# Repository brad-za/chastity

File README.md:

# Chastity Keyboard - Choc v1

A wireless split ergonomic keyboard featuring Kailh Choc v1 low-profile switches, rotary encoders, and ZMK firmware.

## Features

- **Split Design**: Ergonomic 30-key split layout per half (60 keys total)
- **Wireless**: Powered by nice!nano v2 controllers with ZMK firmware
- **Low Profile**: Kailh Choc v1 switches for a sleek, portable design
- **Rotary Encoders**: One encoder per half for volume/scroll control
- **Hot-swap**: Choc v1 hot-swap sockets for easy switch replacement
- **Battery Powered**: Individual LiPo batteries for each half
- **Power Management**: Individual power switches per half

## Bill of Materials (BOM)

### Electronics & Controllers
| Component | Quantity | Description | Notes |
|-----------|----------|-------------|-------|
| nice!nano v2 | 2 | Wireless microcontroller | One per half |
| LiPo Battery | 2 | 3.7V 110-301230 or similar | ~110mAh recommended |
| JST PH 2-pin Connector | 2 | Battery connector | For nice!nano battery connection |

### Switches & Keycaps
| Component | Quantity | Description | Notes |
|-----------|----------|-------------|-------|
| Kailh Choc v1 Switches | 60 | Low-profile mechanical switches | Any Choc v1 variant |
| Choc v1 Keycaps (1u) | 54 | Standard 1u keycaps | |
| Choc v1 Keycaps (1u) | 2 | Indexed 1u keycaps | F & J keys |
| Choc v1 Keycaps (1.25u) | 2 | Pinky key keycaps | For control buttons cluster |
| Choc v1 Keycaps (1.5u) | 2 | Thumb key keycaps | For thumb cluster |

### Electronic Components
| Component | Quantity | Description | Package | Notes |
|-----------|----------|-------------|---------|-------|
| Diodes | 60 | 1N4148W or similar | SOD-123 | One per switch |
| Rotary Encoder | 2 | Alps EC11E series | Through-hole | With push switch |
| Power Switch | 2 | SPDT slide switch | PCM12 package | Individual power control |
| Choc v1 Hot-swap Sockets | 60 | Kailh hot-swap sockets | | One per switch position |

### PCBs & Hardware
| Component | Quantity | Description | Notes |
|-----------|----------|-------------|-------|
| Chastity PCB Left | 1 | Main PCB for left half | Fabricate from KiCad files |
| Chastity PCB Right | 1 | Main PCB for right half | Fabricate from KiCad files |
| Case Components | 1 set | Laser-cut case files | Optional - see cases/choc/v1/ |

### Optional Components
| Component | Quantity | Description | Notes |
|-----------|----------|-------------|-------|
| USB-C Cable | 2 | Charging/programming | Standard USB-C cables |

## Assembly Instructions

### 1. PCB Preparation
1. Inspect PCBs for any manufacturing defects
2. Clean flux residue if necessary

### 2. SMD Component Soldering
1. **Diodes**: Solder all 60 diodes (30 per PCB) in SOD-123 packages
   - Pay attention to polarity markings on the PCB
   - Cathode (marked end) should align with the line on the PCB silkscreen

### 3. Through-hole Components
1. **Hot-swap sockets**: Install all 60 Choc v1 hot-swap sockets
   - Ensure proper alignment before soldering
   - Apply flux for clean joints
2. **Rotary encoders**: Install one Alps EC11E encoder per PCB
   - Ensure proper seating before soldering
3. **Power switches**: Install PCM12 slide switches
4. **Battery connectors**: Install JST PH 2-pin connectors

### 4. Controller Installation
1. **Socket installation** (recommended):
   - Install mill-max sockets for nice!nano controllers
   - This allows for easy removal/replacement
2. **nice!nano mounting**:
   - Install nice!nano v2 controllers with components facing down
   - Ensure proper pin alignment

### 5. Switch Installation
1. Install Kailh Choc v1 switches into hot-swap sockets
2. Ensure switches are fully seated and secure
3. Test each switch for proper actuation

### 6. Keycap Installation
1. Install keycaps on all switches
2. Use 1.25u keycaps for thumb cluster keys

## Firmware

This keyboard uses ZMK firmware with configurations located in `code/zmk/`.

### Flashing Firmware

#### Initial Setup
1. Connect nice!nano via USB-C
2. Put controller in bootloader mode (double-tap reset)
3. Flash the appropriate firmware:
   - `chastity_left-nice_nano_v2-zmk.uf2` for left half
   - `chastity_right-nice_nano_v2-zmk.uf2` for right half

#### Building Custom Firmware
1. Fork the ZMK config repository
2. Modify keymap in `config/chastity.keymap`
3. GitHub Actions will automatically build firmware
4. Download and flash the generated `.uf2` files

### Keymap Configuration

The keymap lives at `code/zmk/boards/shields/chastity/chastity.keymap`. Four layers are defined:

| # | Name     | Purpose                                                                                                              |
|---|----------|----------------------------------------------------------------------------------------------------------------------|
| 0 | DEFAULT  | QWERTY base layer.                                                                                                   |
| 1 | NUMPAD   | F-keys on the top row, numpad cluster on the right hand, shifted-symbol cluster on the left. Toggle with `tog NUMPAD`. |
| 2 | NAV      | Caps Lock + media controls on the top-left, arrow / Home / End cluster on the right hand, **Bluetooth controls on the top-right row**. Toggle with `tog NAV`. |
| 3 | GAMING   | Shifts the left half one column to the right so physical WASD outputs ESDF; the now-blank inner column gets right-side letters (P / L / M / O / I / U) so the right hand isn't needed while gaming. Toggle with the chord **RCTRL + RET (right thumb) + P**. |

#### Encoders

| Encoder | Rotation                       | Press (matrix-shared with the inner thumb key)            |
|---------|--------------------------------|------------------------------------------------------------|
| Left    | Mouse scroll wheel up / down   | `F24` — useful for binding push-to-talk or stream macros   |
| Right   | Volume up / down               | `C_MUTE`                                                   |

The encoder press position shares its matrix net with the inner-thumb key on each half — so pressing the inner thumb fires the same key as the encoder click.

#### Bluetooth controls (on NAV layer, top-right row, inner → outer)

```
out OUT_TOG | bt BT_SEL 0 | bt BT_SEL 1 | bt BT_SEL 2 | bt BT_SEL 3 | bt BT_CLR
```

- `OUT_TOG` toggles output between USB and BLE
- `BT_SEL 0..3` switches between four paired hosts
- `BT_CLR` clears the bond on the currently selected profile (use this to re-pair). Placed at the outer edge so it isn't pressed by accident.

#### BLE name

The keyboard advertises as **`Chastity`** (set in `Kconfig.defconfig`). The right half advertises as `Chastity Right` to the central only — your host never sees it.

## Case Options

Case files are available in the `cases/choc/v1/` directory:
- `chastity-bottom-left.dxf` / `chastity-bottom-right.dxf` - Bottom plates
- `chastity-bb-left.dxf` / `chastity-bb-right.dxf` - Switch plates

### Case Assembly
1. Laser cut case components from 3mm acrylic or similar
2. Use M3 standoffs and screws for assembly
3. Install rubber feet for stability

## Suppliers & Part Numbers

### Electronics
- **nice!nano v2**: [Typeractive](https://typeractive.xyz/products/nice-nano), [splitkb.com](https://splitkb.com)
- **Batteries**: Search for "110mAh 3.7V LiPo" on electronics suppliers
- **Diodes**: 1N4148W from Digikey, Mouser, LCSC
- **Encoders**: Alps EC11E15244G1 or similar

### Mechanical Components
- **Choc v1 Switches**: [NovelKeys](https://novelkeys.com), [splitkb.com](https://splitkb.com)
- **Choc Keycaps**: [MBK keycaps](https://mkultra.click/mbk-choc-keycaps), [splitkb.com](https://splitkb.com)
- **Hot-swap Sockets**: Kailh Choc v1 sockets from mechanical keyboard suppliers

### PCB Fabrication
Upload the Gerber files from `kicad/choc/v1/` to:
- **JLCPCB**: Cost-effective option
- **PCBWay**: Good quality and service
- **OSH Park**: US-based, high quality

## Troubleshooting

### Common Issues
1. **Switch not registering**: Check diode polarity and solder joints
2. **Encoder not working**: Verify encoder orientation and pin connections
3. **Battery not charging**: Check JST connector polarity and nice!nano installation
4. **Wireless connection issues**: Re-pair devices, check ZMK configuration

### Support
- Check ZMK documentation: [zmk.dev](https://zmk.dev)
- Review schematic files in `kicad/choc/v1/`
- Verify component placement against PCB silkscreen

## License

This project is open source. PCB designs, case files, and firmware configurations are available for personal and educational use.

## Changelog

### v1.0
- Initial release with Choc v1 support
- ZMK firmware configuration
- Complete build documentation

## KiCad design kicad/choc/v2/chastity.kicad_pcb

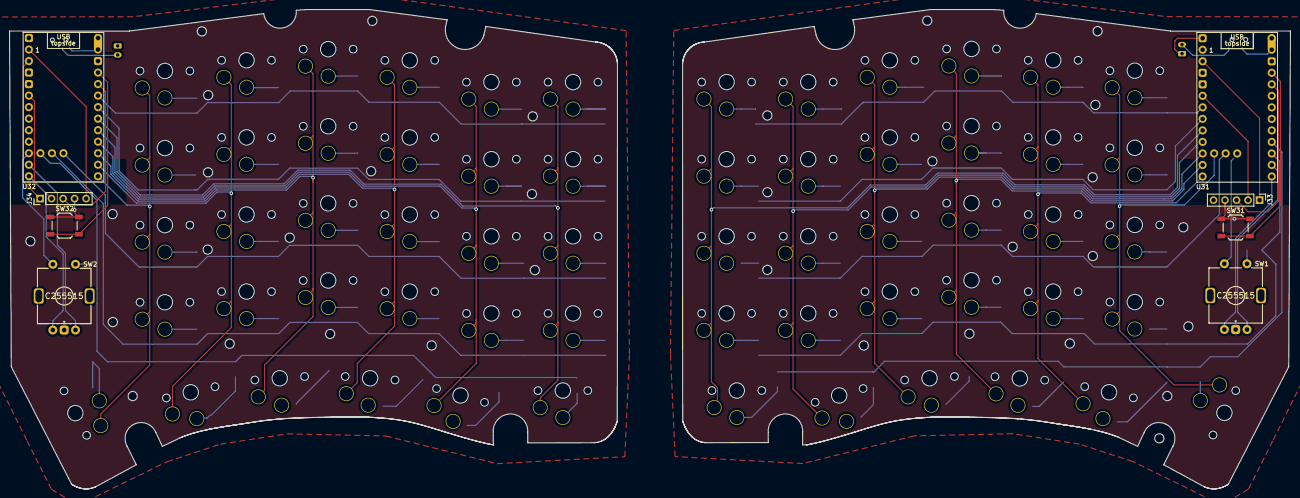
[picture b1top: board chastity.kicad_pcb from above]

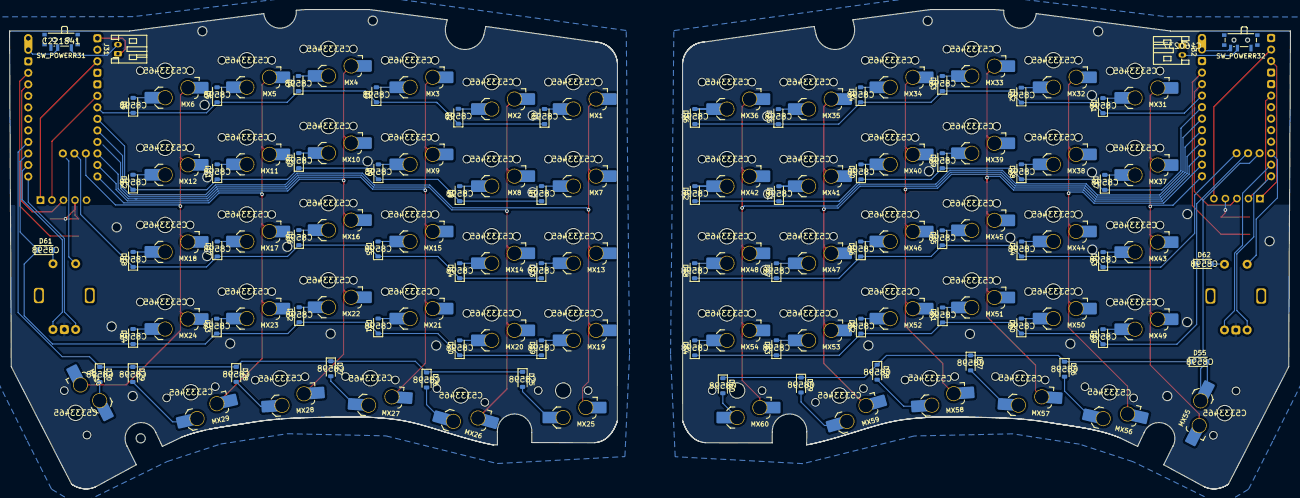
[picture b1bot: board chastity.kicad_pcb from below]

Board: 2 copper layers, 282.4 x 105.7 mm, 134 parts (126 on the bottom side), 107 nets.

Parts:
D1, D2, D3, D4, D5, D6, D7, D8, D9, D10, D11, D12, D13, D14, D15, D16, D17, D18, D19, D20, D21, D22, D23, D24, D25, D26, D27, D28, D29, D30, D31, D32, D33, D34, D35, D36, D37, D38, D39, D40, D41, D42, D43, D44, D45, D46, D47, D48, D49, D50, D51, D52, D53, D54, D55, D56, D57, D58, D59, D60, D61, D62: D_Small; D_SOD-123
J31, J32: Conn_01x02_Socket; JST_PH_S2B-PH-K_1x02_P2.00mm_Horizontal
J33, J34: Conn_01x05_Socket; PinHeader_1x05_P2.54mm_Vertical
MX1, MX2, MX3, MX4, MX5, MX6, MX7, MX8, MX9, MX10, MX11, MX12, MX13, MX14, MX15, MX16, MX17, MX18, MX19, MX20, MX21, MX22, MX23, MX24, MX26, MX27, MX28, MX29, MX30, MX31, MX32, MX33, MX34, MX35, MX36, MX37, MX38, MX39, MX40, MX41, MX42, MX43, MX44, MX45, MX46, MX47, MX48, MX49, MX50, MX51, MX52, MX53, MX54, MX55, MX56, MX57, MX58, MX59: MX_SW_HS; SW_choc_v1_HS_CPG135001S30_1u
MX25, MX60: MX_SW_HS; SW_choc_v1_HS_CPG135001S30_1.25u
SW1, SW2: RotaryEncoder_Switch; ROT_Alps_EC11E-Switch
SW31, SW32: SW_Push; SW_SPST_TL3342
SW_POWERR31, SW_POWERR32: SW_SPDT; SW_SPDT_PCM12
U31, U32: nice_nano; nice_nano_AH_USBup

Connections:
GND: J33.4, J34.4, SW1.C, SW2.C, SW31.1, SW32.1
unnamed: D1.2 (A), MX1.2
unnamed: D2.2 (A), MX2.2
unnamed: D3.2 (A), MX3.2
unnamed: D4.2 (A), MX4.2
unnamed: D5.2 (A), MX5.2
unnamed: D6.2 (A), MX6.2
unnamed: D7.2 (A), MX7.2
unnamed: D8.2 (A), MX8.2
unnamed: D9.2 (A), MX9.2
unnamed: D10.2 (A), MX10.2
unnamed: D11.2 (A), MX11.2
unnamed: D12.2 (A), MX12.2
unnamed: D13.2 (A), MX13.2
unnamed: D14.2 (A), MX14.2
unnamed: D15.2 (A), MX15.2
unnamed: D16.2 (A), MX16.2
unnamed: D17.2 (A), MX17.2
unnamed: D18.2 (A), MX18.2
unnamed: D19.2 (A), MX19.2
unnamed: D20.2 (A), MX20.2
unnamed: D21.2 (A), MX21.2
unnamed: D22.2 (A), MX22.2
unnamed: D23.2 (A), MX23.2
unnamed: D24.2 (A), MX24.2
unnamed: D25.2 (A), MX25.2
unnamed: D26.2 (A), MX26.2
unnamed: D27.2 (A), MX27.2
unnamed: D28.2 (A), MX28.2
unnamed: D29.2 (A), MX29.2
unnamed: D30.2 (A), MX30.2
unnamed: D31.2 (A), MX31.2
unnamed: D32.2 (A), MX32.2
unnamed: D33.2 (A), MX33.2
unnamed: D34.2 (A), MX34.2
unnamed: D35.2 (A), MX35.2
unnamed: D36.2 (A), MX36.2
unnamed: D37.2 (A), MX37.2
unnamed: D38.2 (A), MX38.2
unnamed: D39.2 (A), MX39.2
unnamed: D40.2 (A), MX40.2
unnamed: D41.2 (A), MX41.2
unnamed: D42.2 (A), MX42.2
unnamed: D43.2 (A), MX43.2
unnamed: D44.2 (A), MX44.2
unnamed: D45.2 (A), MX45.2
unnamed: D46.2 (A), MX46.2
unnamed: D47.2 (A), MX47.2
unnamed: D48.2 (A), MX48.2
unnamed: D49.2 (A), MX49.2
unnamed: D50.2 (A), MX50.2
unnamed: D51.2 (A), MX51.2
unnamed: D52.2 (A), MX52.2
unnamed: D53.2 (A), MX53.2
unnamed: D54.2 (A), MX54.2
unnamed: D55.2 (A), MX55.2
unnamed: D56.2 (A), MX56.2
unnamed: D57.2 (A), MX57.2
unnamed: D58.2 (A), MX58.2
unnamed: D59.2 (A), MX59.2
unnamed: D60.2 (A), MX60.2
unnamed: D61.2 (A), SW1.S1
unnamed: D62.2 (A), SW2.S1
unnamed: J31.1, U31.28 (GND)
unnamed: J31.2, SW_POWERR31.1 (A)
unnamed: J32.1, U32.28 (GND)
unnamed: J32.2, SW_POWERR32.2 (B)
unnamed: J33.3, U31.16 (3V3)
unnamed: J34.3, U32.16 (3V3)
unnamed: SW_POWERR31.2 (B), U31.13 (BAT+)
unnamed: SW_POWERR32.3 (C), U32.13 (BAT+)
unnamed: SW31.2, U31.15 (RST)
unnamed: SW32.2, U32.15 (RST)
SCLK: J33.2, U31.5 (P0.17)
SCLK_R: J34.2, U32.5 (P0.17)
SCS: J33.5, U31.1 (P0.06)
SCS_R: J34.5, U32.1 (P0.06)
SI: J33.1, U31.2 (P0.08)
SI_R: J34.1, U32.2 (P0.08)
col 0: SW2.S2, U32.10 (P0.11)
col 1: MX31.1, MX37.1, MX43.1, MX49.1, MX55.1, U32.24 (P0.09-LF)
col 2: MX32.1, MX38.1, MX44.1, MX50.1, MX56.1, U32.23 (P0-10-LF)
col 3: MX33.1, MX39.1, MX45.1, MX51.1, MX57.1, U32.22 (P1.11-LF)
col 4: MX34.1, MX40.1, MX46.1, MX52.1, MX58.1, U32.21 (P1.13-LF)
col 5: MX35.1, MX41.1, MX47.1, MX53.1, MX59.1, U32.20 (P1.15-LF)
col 6: MX36.1, MX42.1, MX48.1, MX54.1, MX60.1, U32.19 (P0.02-LF)
col_0_l: SW1.S2, U31.27 (P1-07-LF)
col_1_l: MX6.1, MX12.1, MX18.1, MX24.1, MX30.1, U31.25 (P1.01-LF)
col_2_l: MX5.1, MX11.1, MX17.1, MX23.1, MX29.1, U31.12 (P1.06-LF)
col_3_l: MX4.1, MX10.1, MX16.1, MX22.1, MX28.1, U31.11 (P1.04-LF)
col_4_l: MX3.1, MX9.1, MX15.1, MX21.1, MX27.1, U31.10 (P0.11)
col_5_l: MX2.1, MX8.1, MX14.1, MX20.1, MX26.1, U31.9 (P1.00)
col_6_l: MX1.1, MX7.1, MX13.1, MX19.1, MX25.1, U31.8 (P0.24)
rot_a: SW2.A, U32.12 (P1.06-LF)
rot_a_l: SW1.A, U31.24 (P0.09-LF)
rot_b: SW2.B, U32.11 (P1.04-LF)
rot_b_l: SW1.B, U31.23 (P0-10-LF)
row_0: D55.1 (K), D56.1 (K), D57.1 (K), D58.1 (K), D59.1 (K), D60.1 (K), U32.25 (P1.01-LF)
row_0_l: D25.1 (K), D26.1 (K), D27.1 (K), D28.1 (K), D29.1 (K), D30.1 (K), U31.21 (P1.13-LF)
row_1: D49.1 (K), D50.1 (K), D51.1 (K), D52.1 (K), D53.1 (K), D54.1 (K), D62.1 (K), U32.26 (P1.02-LF)
row_1_l: D19.1 (K), D20.1 (K), D21.1 (K), D22.1 (K), D23.1 (K), D24.1 (K), D61.1 (K), U31.22 (P1.11-LF)
row_2: D43.1 (K), D44.1 (K), D45.1 (K), D46.1 (K), D47.1 (K), D48.1 (K), U32.27 (P1-07-LF)
row_2_l: D13.1 (K), D14.1 (K), D15.1 (K), D16.1 (K), D17.1 (K), D18.1 (K), U31.26 (P1.02-LF)
row_3: D37.1 (K), D38.1 (K), D39.1 (K), D40.1 (K), D41.1 (K), D42.1 (K), U32.18 (P0.29-LF)
row_3_l: D7.1 (K), D8.1 (K), D9.1 (K), D10.1 (K), D11.1 (K), D12.1 (K), U31.7 (P0.22)
row_4: D31.1 (K), D32.1 (K), D33.1 (K), D34.1 (K), D35.1 (K), D36.1 (K), U32.17 (P0.31-LF)
row_4_l: D1.1 (K), D2.1 (K), D3.1 (K), D4.1 (K), D5.1 (K), D6.1 (K), U31.6 (P0.20)

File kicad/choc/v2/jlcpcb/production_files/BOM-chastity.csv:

Comment,Designator,Footprint,LCSC
Conn_01x02_Socket,"J31,J32",JST_PH_S2B-PH-K_1x02_P2.00mm_Horizontal,C160237
SW_SPDT,"SW_POWERR31,SW_POWERR32",SW_SPDT_PCM12,C221841
RotaryEncoder_Switch,"SW1,SW2",ROT_Alps_EC11E-Switch,C255515
MX_SW_HS,"MX1,MX10,MX11,MX12,MX13,MX14,MX15,MX16,MX17,MX18,MX19,MX2,MX20,MX21,MX22,MX23,MX24,MX26,MX27,MX28,MX29,MX3,MX30,MX31,MX32,MX33,MX34,MX35,MX36,MX37,MX38,MX39,MX4,MX40,MX41,MX42,MX43,MX44,MX45,MX46,MX47,MX48,MX49,MX5,MX50,MX51,MX52,MX53,MX54,MX55,MX56,MX57,MX58,MX59,MX6,MX7,MX8,MX9",SW_choc_v1_HS_CPG135001S30_1u,C5333465
D_Small,"D1,D10,D11,D12,D13,D14,D15,D16,D17,D18,D19,D2,D20,D21,D22,D23,D24,D25,D26,D27,D28,D29,D3,D30,D31,D32,D33,D34,D35,D36,D37,D38,D39,D4,D40,D41,D42,D43,D44,D45,D46,D47,D48,D49,D5,D50,D51,D52,D53,D54,D55,D56,D57,D58,D59,D6,D60,D61,D62,D7,D8,D9",D_SOD-123,C8598
MX_SW_HS,MX60,SW_choc_v1_HS_CPG135001S30_1.25u,
MX_SW_HS,MX25,SW_choc_v1_HS_CPG135001S30_1.25u,

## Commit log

2023-11-14 added TFT and centered master USBC
    The case also got changed to accept the new TFT
2025-07-24 updated files to store all my work
2025-07-24 added zmk code to the big repo
2026-05-07 house keeping
2026-05-08 working no encoder
2026-06-24 works
